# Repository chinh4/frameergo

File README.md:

# frameergo

An ergonomic laptop based off of the framework 13, based off of the concept by the Evan and Katelyn youtube channel. It will feature a keyboard based on the ferris sweep (though modified), and an adjustable display.

---

## Renders

images that look somewhat nice hopefully

---

## how use??!1/?

Put it together and enjoy... its pretty self explanatory. You can pivot the screen however you wish, as long as the cables reach.

CAD found [here](https://cad.onshape.com/documents/80817440b3423ec8b1940df3/w/df84cddcf0cb2965e0230ab6/e/d5c515e039b8b80401e512cd)

---

## but... why?

Why not? lol. More realistically, I wanted to do a project that challenged my current skillset and allow me to grow from it. Mainly with KiCAD and CAD in general.

---

## Frameortho (The keyboard)

---

## Display Adapters

---

## USB Hub

---

## BOM

| Item                          | Quantity             | Price (USD)   | Link                                                                                        | Description                       |
|:------------------------------|:---------------------|:--------------|:--------------------------------------------------------------------------------------------|:----------------------------------|
| PCB + Stencil (Sink + Source) | 5                    | $14.11        | https://jlcpcb.com/                                                                         | PCB for adapters                  |
| Display Port Cable            | 1                    | $7.50         | https://www.amazon.com/dp/B01J8S6X2I                                                        | Display Port cable                |
| 20455-040E-76                 | 2                    | $4.42         | https://www.digikey.com/en/products/detail/i-pex/20455-040E-76/22108829                     | EDP connector                     |
| XT30 (2+2) Right Male         | 2                    | $4.08         | https://www.aliexpress.us/item/3256804674449127.html                                        | Connector for power wires         |
| XT30 (2+2) Right Female       | 2                    | $4.44         | https://www.aliexpress.us/item/3256804674449127.html                                        | Connector for power               |
| Molex 0472720001              | 2                    | $11.06        | https://www.digikey.com/en/products/detail/molex/0472720001/1765727                         | Display Port connector            |
| EDP Cable                     | 1                    | $4.62         | https://www.aliexpress.us/item/3256806626687023.html                                        | EDP cable for display             |
| Flex PCB + Stencil            | 5                    | $5.05         | https://jlcpcb.com/                                                                         | USB Hub Flex Cable                |
| CY7C65634-28LTXC              | 5                    | $12.25        | https://www.digikey.com/en/products/detail/infineon-technologies/CY7C65634-28LTXC/2805204   | USB Hub IC                        |
| RR1220P-102-D                 | 10                   | $0.31         | https://www.digikey.com/en/products/detail/susumu/RR1220P-102-D/432291                      | 1k ohm resistor                   |
| CRCW080510K0FKEA              | 10                   | $0.41         | https://www.digikey.com/en/products/detail/vishay-dale/CRCW080510K0FKEA/1175751             | 10k ohm resistor                  |
| C0805C104K5RACTU              | 10                   | $0.16         | https://www.digikey.com/en/products/detail/kemet/C0805C104K5RACTU/411169                    | CAP CER 0.1UF 50V X7R 0805        |
| RMCF0805ZT0R00                | 10                   | $0.06         | https://www.digikey.com/en/products/detail/stackpole-electronics-inc/RMCF0805ZT0R00/1756901 | RES 0 OHM JUMPER 1/8W 0805        |
| ABM3B-12.000MHZ-B2-T          | 5                    | $3.35         | https://www.digikey.com/en/products/detail/abracon-llc/ABM3B-12-000MHZ-B2-T/675311          | CRYSTAL 12.0000MHZ 18PF SMD       |
| CC0805JRNPO9BN270             | 10                   | $0.48         | https://www.digikey.com/en/products/detail/yageo/CC0805JRNPO9BN270/302838                   | CAP CER 27PF 50V C0G/NPO 0805     |
| LMK212BJ106KG-T               | 10                   | $0.16         | https://www.digikey.com/en/products/detail/taiyo-yuden/LMK212BJ106KG-T/930652               | CAP CER 10UF 10V X5R 0805         |
| 046809610110846+              | 4                    | $2.84         | https://www.digikey.com/en/products/detail/kyocera-avx/046809610110846/10313169             | Power button connector            |
| PCB + PCBA                    | 2 (PCBA) + 3 (Blank) | $45.30        | https://jlcpcb.com/                                                                         | Keyboard PCB                      |
| PG1316S                       | 40                   | $30.00        | https://modulo.industries/product/pg1316s-switch/                                           | Keyswitches                       |
| SOD-123 Diode                 | 40                   | $30.00        | https://typeractive.xyz/products/smd-diodes                                                 | Diodes                            |
| TL3342                        | 2                    | $1.16         | https://www.digikey.com/en/products/base-product/e-switch/141/TL3342/472571                 | Buttons for boot and reset        |
| PG1316 Keycaps                | 4                    | $18.00        | https://holykeebs.com/products/kailh-pg1316s-keycaps?variant=49205120270626                 | Keycaps for keyswitches           |
| PETG Filament                 | 2                    | $24.99        | https://www.amazon.com/SUNLU-Filament-Strength-Dimensional-Accuracy/dp/B0FRRX8YDF           | Filament for case                 |
| Framework 13 Motherboard      | 1                    | Varies        | https://frame.work/marketplace/mainboards                                                   | Motherboard                       |
| Invisible Selfie Stick        | 4                    | $21.62        | https://www.aliexpress.us/item/3256805833609538.html                                        | For hinges and screen support     |
| Threaded bumper               | 2                    | $9.40         | https://www.mcmaster.com/9546K551/                                                          | For screen support                |
| 1/4 threaded inserts          | 1                    | $10.49        | https://www.amazon.com/dp/B08PVQX853                                                        | For screen frame                  |
| 1/4 Screw                     | 1                    | $8.49         | https://www.amazon.com/ThtRht-Replace-Handheld-Stabilizer-Extension/dp/B0FSRK4FYH           | For putting screen frame together |
| 1/4 x 1 - 1/2" Screw          | 1                    | $8.99         | https://www.amazon.com/Socket-Screws-Countersunk-Stainless-Thread/dp/B08QJ67SFG             | For putting hinges on             |
| 1/4 Nut                       | 1                    | $4.99         | https://www.amazon.com/Juvielich-4-20-Stainless-Fasteners-Replacement/dp/B0CSY9G7TW         | For putting hinges on             |
| Framework 13 Battery          | 1                    | $69.00        | https://frame.work/products/battery?v=FRANGWAT01                                            | Battery                           |
| Framework 13 Power Button     | 1                    | $29.00        | https://frame.work/products/fingerprint-reader-kit?v=FRANTD0001                             | Power button                      |
| Framework 13 Touchpad         | 1                    | $39.00        | https://frame.work/products/touchpad-kit?v=FRANFT0001                                       | Touchpad                          |
| Framework 13 Screen           | 1                    | $159.00       | https://frame.work/products/display-kit?v=FRANGX0001                                        | Screen                            |
| Framework 13 Audio Board      | 1                    | $14.00        | https://frame.work/products/audio-board-kit?v=FRANFY0001                                    | Audio board                       |
| Framework 13 Antenna          | 1                    | $14.00        | https://frame.work/products/antenna-module?v=FRANCXAW01                                     |                                   |
| Total (no tax or shipping):   |                      | $612.73       |                                                                                             |                                   |

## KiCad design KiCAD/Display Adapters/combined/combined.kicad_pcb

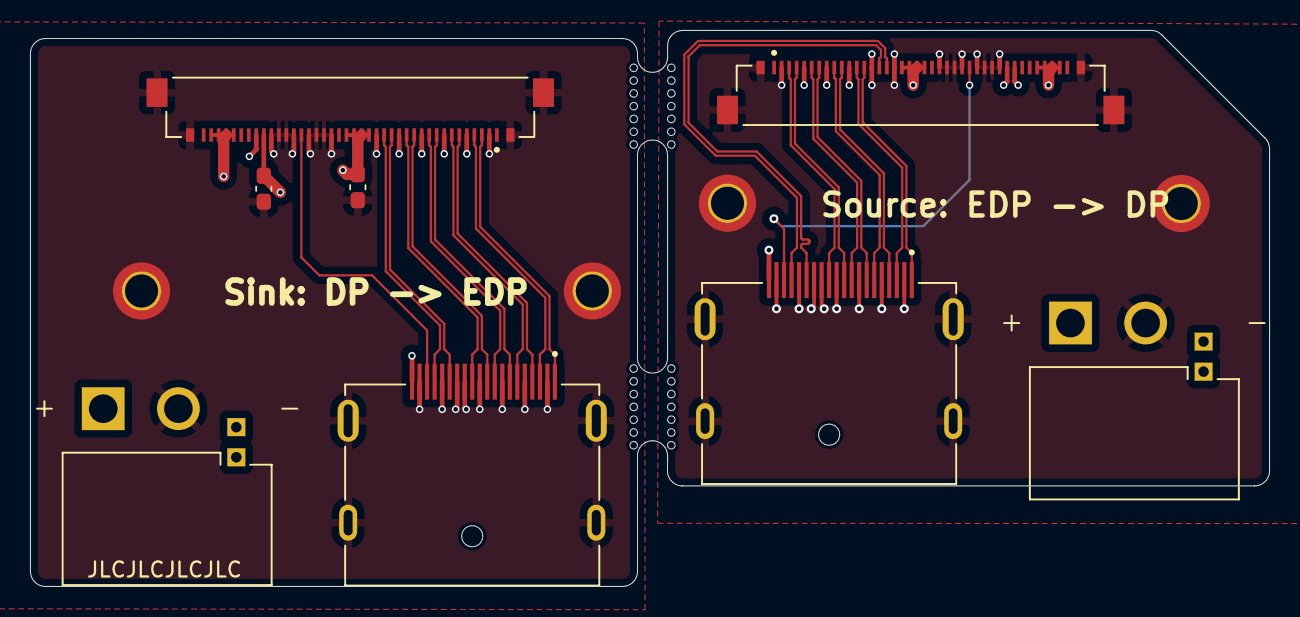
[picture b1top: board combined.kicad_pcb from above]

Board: 4 copper layers, 82.4 x 37.0 mm, 12 parts (0 on the bottom side), 16 nets.

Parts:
C1, C2: 1uF; C_0603_1608Metric_Pad1.08x0.95mm_HandSolder
H1, H1#2, H2, H2#2: MountingHole_Pad; MountingHole_2.2mm_M2_DIN965_Pad_TopBottom
J1, J4: 47272-0001; MOLEX_47272-0001
J2, J5: XT30PW_2_2_-M.G.B; AMASS_XT30PW_2_2_-M.G.B
J3, J6: 20455-040E-76; IPEX_20455-040E-76

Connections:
0_EDP_TX_N: J1.10, J3.12, J4.3, J6.12
0_EDP_TX_P: J1.12, J3.13, J4.1, J6.13
1_EDP_TX_N: J1.7, J3.9, J4.6, J6.9
1_EDP_TX_P: J1.9, J3.10, J4.4, J6.10
2_EDP_TX_N: J1.4, J3.6, J4.9, J6.6
2_EDP_TX_P: J1.6, J3.7, J4.7, J6.7
3_EDP_TX_N: J1.1, J3.3, J4.12, J6.3
3_EDP_TX_P: J1.3, J3.4, J4.10, J6.4
+3.3V: C1.1, J1.20, J3.18, J3.19, J3.20, J3.21, J4.20, J6.18, J6.19, J6.20, J6.21
+5V: J2.P, J3.36, J3.37, J3.38, J3.39, J5.P, J6.36, J6.37, J6.38, J6.39
AUX_N: J1.17, J3.16, J4.17, J6.16
AUX_P: J1.15, J3.15, J4.15, J6.15
BLK_OFF_N: C2.2, J2.S1, J3.32, J5.S1, J6.32
BLK_PWM_LCD: J2.S2, J3.33, J5.S2, J6.33
EDP_HPD: J1.18, J3.27, J4.18, J6.27
GND: C1.2, C2.1, H1.1, H1#2.1, H2.1, H2#2.1, J1.2, J1.5, J1.8, J1.11, J1.13, J1.14, J1.16, J1.19, J1.S1 (SHIELD), J1.S2 (SHIELD), J1.S3 (SHIELD), J1.S4 (SHIELD), J2.N, J3.2, J3.5, J3.8, J3.11, J3.14, J3.17, J3.23, J3.24, J3.25, J3.26, J3.28, J3.29, J3.30, J3.31, J3.S1 (SHIELD), J3.S2 (SHIELD), J3.S3 (SHIELD), J3.S4 (SHIELD), J4.2, J4.5, J4.8, J4.11, J4.13, J4.14, J4.16, J4.19, J4.S1 (SHIELD), J4.S2 (SHIELD), J4.S3 (SHIELD), J4.S4 (SHIELD), J5.N, J6.2, J6.5, J6.8, J6.11, J6.14, J6.17, J6.23, J6.24, J6.25, J6.26, J6.28, J6.29, J6.30, J6.31, J6.S1 (SHIELD), J6.S2 (SHIELD), J6.S3 (SHIELD), J6.S4 (SHIELD)

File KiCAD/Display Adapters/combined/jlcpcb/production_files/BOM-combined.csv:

Comment,Designator,Footprint,LCSC,Quantity
1uF,"C1,C2",C_0603_1608Metric_Pad1.08x0.95mm_HandSolder,C14663,2
20455-040E-76,"J3,J6",IPEX_20455-040E-76,C5160883,2
47272-0001,"J1,J4",MOLEX_47272-0001,C587824,2

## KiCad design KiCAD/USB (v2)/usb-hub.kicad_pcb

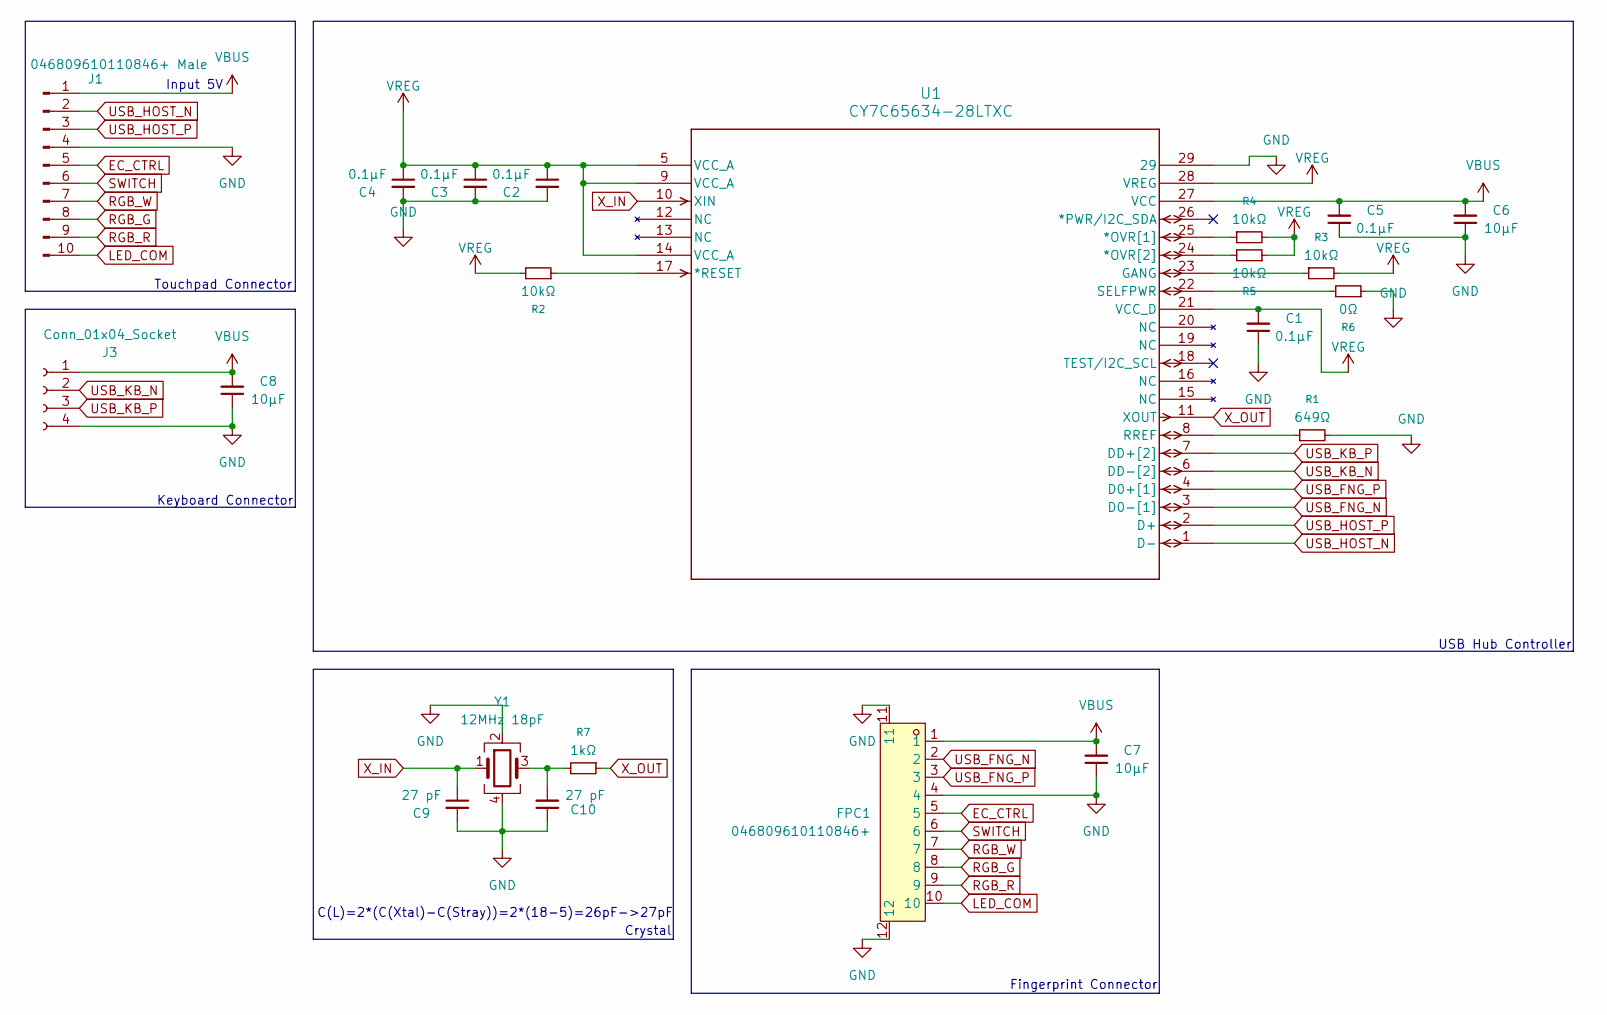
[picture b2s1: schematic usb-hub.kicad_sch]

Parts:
C1, C2, C3, C4, C5: 0.1μF; C_0805_2012Metric_Pad1.18x1.45mm_HandSolder
C6, C7, C8: 10μF; C_0805_2012Metric_Pad1.18x1.45mm_HandSolder
C9, C10: 27 pF; C_0805_2012Metric_Pad1.18x1.45mm_HandSolder
FPC1: 046809610110846+; CONN-SMD_10P-P0.50_046809610110846; LCSC Part C5464531
J1: 046809610110846+ Male; Kyocera_046809610110846+_PCB_Edge
J3: Conn_01x04_Socket; 4 pad
R1: 649Ω; R_0805_2012Metric_Pad1.20x1.40mm_HandSolder
R2, R3, R4, R5: 10kΩ; R_0805_2012Metric_Pad1.20x1.40mm_HandSolder
R6: 0Ω; R_0805_2012Metric_Pad1.20x1.40mm_HandSolder
R7: 1kΩ; R_0805_2012Metric_Pad1.20x1.40mm_HandSolder
U1: CY7C65634-28LTXC; QFN-28
Y1: 12MHz 18pF; Crystal_SMD_Abracon_ABM3B-4Pin_5.0x3.2mm

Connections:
EC_CTRL: FPC1.5, J1.5
GND: C1.1, C2.2, C3.2, C4.2, C5.1, C6.1, C7.1, C8.1, C9.2, C10.1, FPC1.4, FPC1.11, FPC1.12, J1.4, J3.4, R1.2, R6.1, U1.29, Y1.2, Y1.4
LED_COM: FPC1.10, J1.10
unnamed: C10.2, R7.2, Y1.3
unnamed: R4.1, U1.25 (*OVR[1])
unnamed: R5.2, U1.24 (*OVR[2])
unnamed: R2.1, U1.17 (*RESET)
unnamed: R3.1, U1.23 (GANG)
unnamed: R1.1, U1.8 (RREF)
unnamed: R6.2, U1.22 (SELFPWR)
RGB_G: FPC1.8, J1.8
RGB_R: FPC1.9, J1.9
RGB_W: FPC1.7, J1.7
SWITCH: FPC1.6, J1.6
USB_FNG_N: FPC1.2, U1.3 (D0-[1])
USB_FNG_P: FPC1.3, U1.4 (D0+[1])
USB_HOST_N: J1.2, U1.1 (D-)
USB_HOST_P: J1.3, U1.2 (D+)
USB_KB_N: J3.2, U1.6 (DD-[2])
USB_KB_P: J3.3, U1.7 (DD+[2])
VBUS: C5.2, C6.2, C7.2, C8.2, FPC1.1, J1.1, J3.1, U1.27 (VCC)
VREG: C1.2, C2.1, C3.1, C4.1, R2.2, R3.2, R4.2, R5.1, U1.5 (VCC_A), U1.9 (VCC_A), U1.14 (VCC_A), U1.21 (VCC_D), U1.28 (VREG)
X_IN: C9.1, U1.10 (XIN), Y1.1
X_OUT: R7.1, U1.11 (XOUT)

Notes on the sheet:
USB Hub Controller
Keyboard Connector
Crystal
Touchpad Connector
Fingerprint Connector
C(L)=2*(C(Xtal)-C(Stray))=2*(18-5)=26pF->27pF
Input 5V

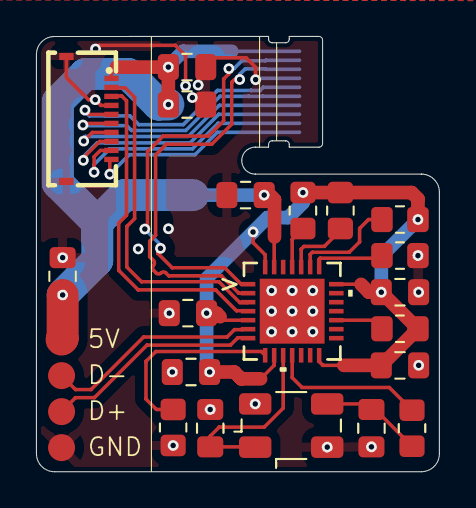
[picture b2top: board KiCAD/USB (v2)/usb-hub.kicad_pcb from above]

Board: 2 copper layers, 22.4 x 24.2 mm, 22 parts (0 on the bottom side), 24 nets.

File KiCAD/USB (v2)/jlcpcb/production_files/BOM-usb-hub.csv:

Comment,Designator,Footprint,LCSC,Quantity
046809610110846+,FPC1,CONN-SMD_10P-P0.50_046809610110846,C5464531,1
CY7C65634-28LTXC,U1,QFN-28,C2951393,1
10kΩ,R5,R_0805_2012Metric_Pad1.20x1.40mm_HandSolder,,1
10kΩ,R4,R_0805_2012Metric_Pad1.20x1.40mm_HandSolder,,1
10kΩ,R2,R_0805_2012Metric_Pad1.20x1.40mm_HandSolder,,1
0.1μF,C4,C_0805_2012Metric_Pad1.18x1.45mm_HandSolder,,1
0.1μF,C5,C_0805_2012Metric_Pad1.18x1.45mm_HandSolder,,1
649Ω,R1,R_0805_2012Metric_Pad1.20x1.40mm_HandSolder,,1
0.1μF,C1,C_0805_2012Metric_Pad1.18x1.45mm_HandSolder,,1
10μF,C8,C_0805_2012Metric_Pad1.18x1.45mm_HandSolder,,1
10kΩ,R3,R_0805_2012Metric_Pad1.20x1.40mm_HandSolder,,1
27 pF,C10,C_0805_2012Metric_Pad1.18x1.45mm_HandSolder,,1
0Ω,R6,R_0805_2012Metric_Pad1.20x1.40mm_HandSolder,,1
12MHz 18pF,Y1,Crystal_SMD_Abracon_ABM3B-4Pin_5.0x3.2mm,,1
0.1μF,C2,C_0805_2012Metric_Pad1.18x1.45mm_HandSolder,,1
27 pF,C9,C_0805_2012Metric_Pad1.18x1.45mm_HandSolder,,1
10μF,C6,C_0805_2012Metric_Pad1.18x1.45mm_HandSolder,,1
1kΩ,R7,R_0805_2012Metric_Pad1.20x1.40mm_HandSolder,,1
0.1μF,C3,C_0805_2012Metric_Pad1.18x1.45mm_HandSolder,,1
10μF,C7,C_0805_2012Metric_Pad1.18x1.45mm_HandSolder,,1

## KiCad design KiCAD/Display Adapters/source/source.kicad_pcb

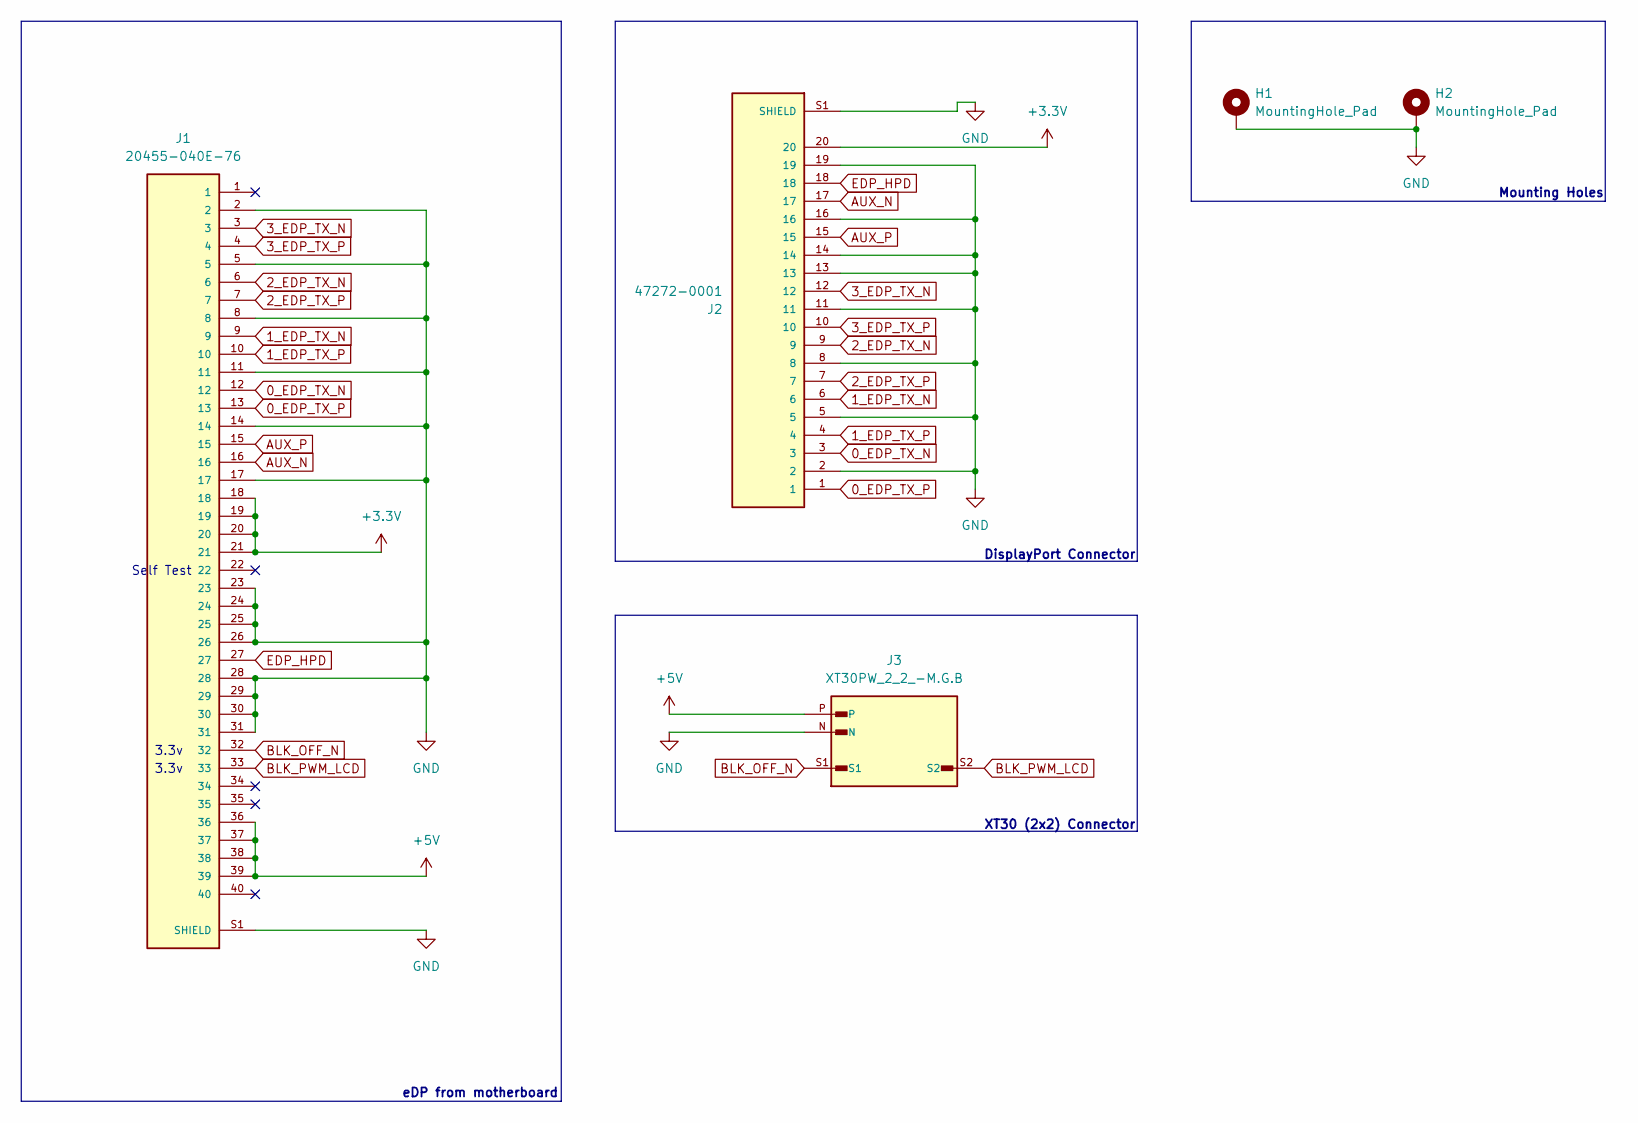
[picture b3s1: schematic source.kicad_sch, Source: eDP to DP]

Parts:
H1, H2: MountingHole_Pad; MountingHole_2.2mm_M2_DIN965_Pad_TopBottom
J1: 20455-040E-76; IPEX_20455-040E-76
J2: 47272-0001; MOLEX_47272-0001
J3: XT30PW_2_2_-M.G.B; AMASS_XT30PW_2_2_-M.G.B; PARTREV NA

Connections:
0_EDP_TX_N: J1.12, J2.3
0_EDP_TX_P: J1.13, J2.1
1_EDP_TX_N: J1.9, J2.6
1_EDP_TX_P: J1.10, J2.4
2_EDP_TX_N: J1.6, J2.9
2_EDP_TX_P: J1.7, J2.7
3_EDP_TX_N: J1.3, J2.12
3_EDP_TX_P: J1.4, J2.10
+3.3V: J1.18, J1.19, J1.20, J1.21, J2.20
+5V: J1.36, J1.37, J1.38, J1.39, J3.P
AUX_N: J1.16, J2.17
AUX_P: J1.15, J2.15
BLK_OFF_N: J1.32, J3.S1
BLK_PWM_LCD: J1.33, J3.S2
EDP_HPD: J1.27, J2.18
GND: H1.1, H2.1, J1.2, J1.5, J1.8, J1.11, J1.14, J1.17, J1.23, J1.24, J1.25, J1.26, J1.28, J1.29, J1.30, J1.31, J1.S1 (SHIELD), J1.S2 (SHIELD), J1.S3 (SHIELD), J1.S4 (SHIELD), J2.2, J2.5, J2.8, J2.11, J2.13, J2.14, J2.16, J2.19, J2.S1 (SHIELD), J2.S2 (SHIELD), J2.S3 (SHIELD), J2.S4 (SHIELD), J3.N

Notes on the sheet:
3.3v
eDP from motherboard
DisplayPort Connector
Mounting Holes
XT30 (2x2) Connector
Self Test

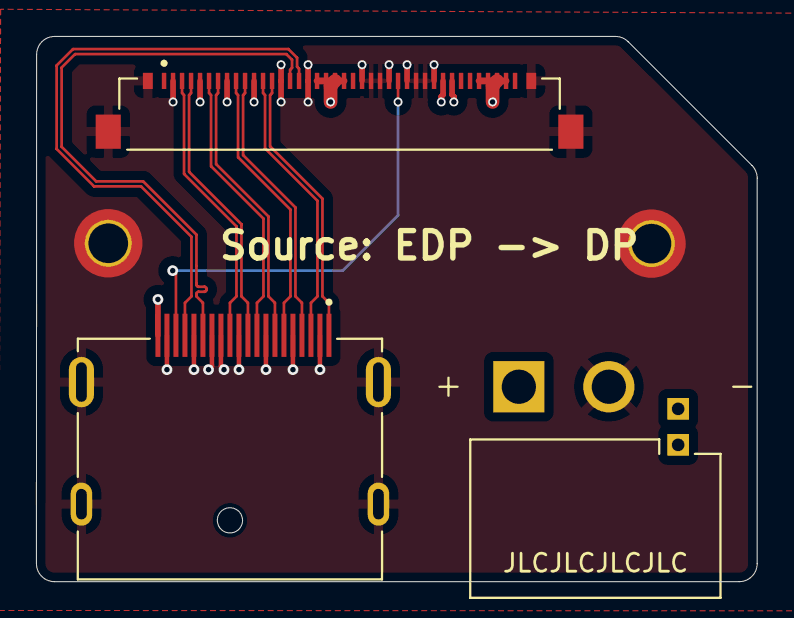
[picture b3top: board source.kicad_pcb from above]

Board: 4 copper layers, 40.0 x 30.3 mm, 5 parts (0 on the bottom side), 16 nets.

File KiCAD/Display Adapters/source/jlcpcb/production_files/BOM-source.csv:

Comment,Designator,Footprint,LCSC,Quantity
20455-040E-76,J1,IPEX_20455-040E-76,C5160883,1
47272-0001,J2,MOLEX_47272-0001,C587824,1

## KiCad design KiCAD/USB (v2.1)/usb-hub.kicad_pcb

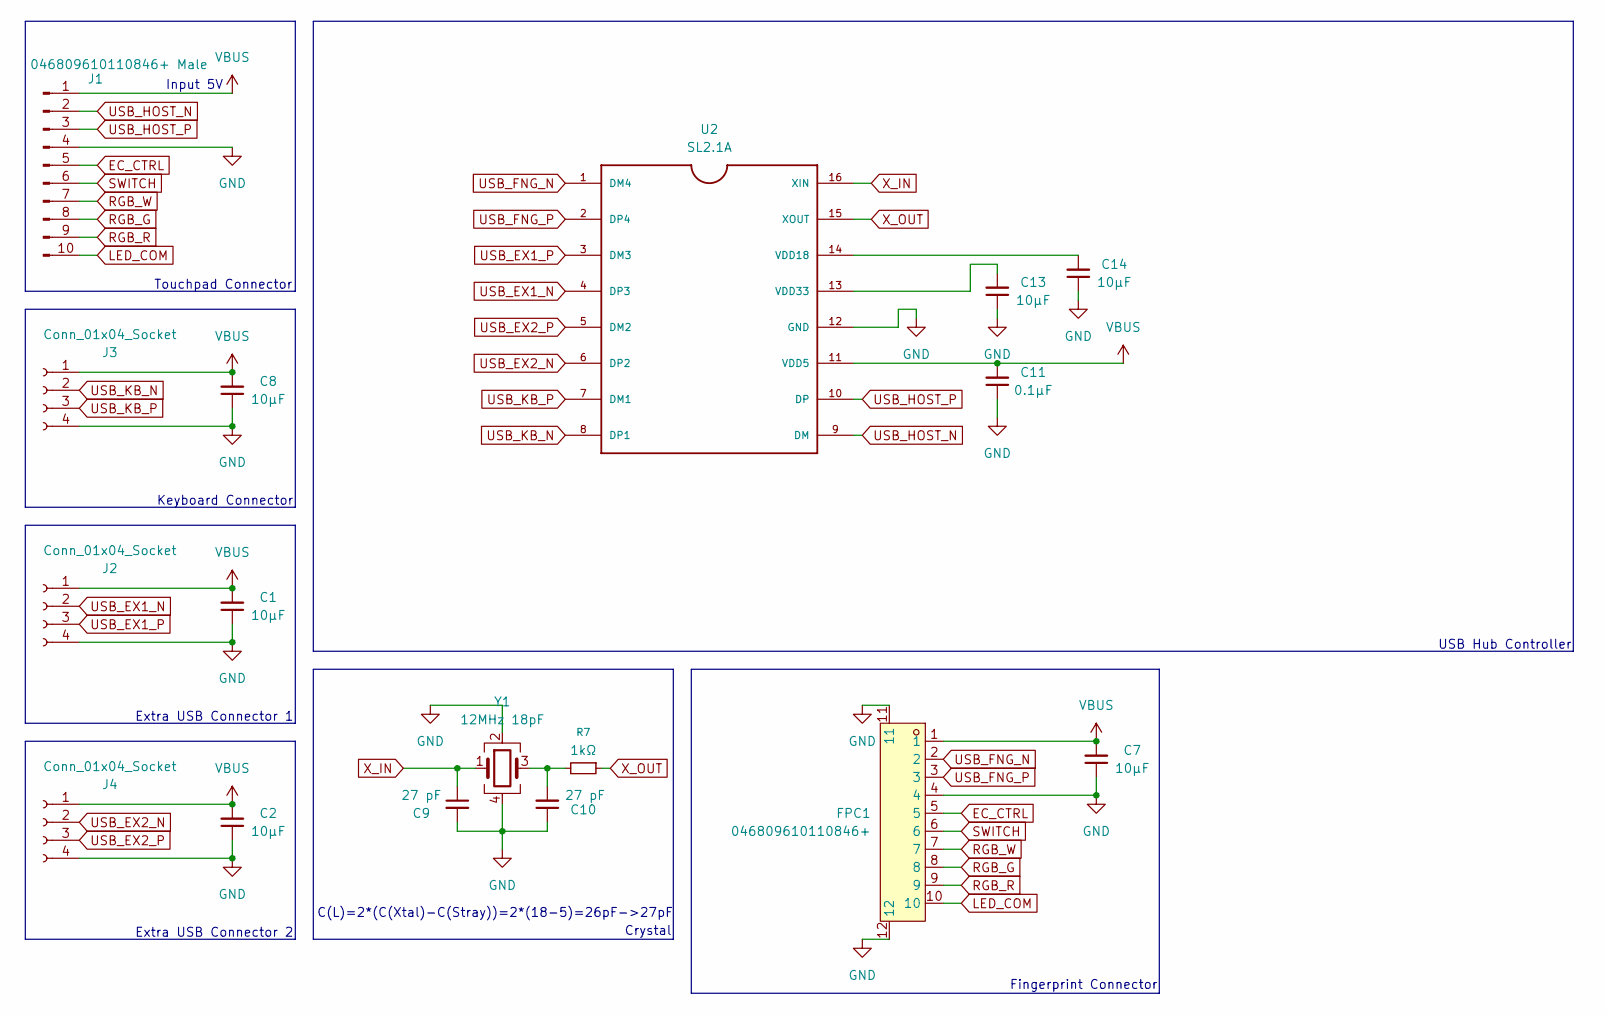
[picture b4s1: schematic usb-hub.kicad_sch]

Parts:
C1, C2, C7, C8, C13, C14: 10μF; C_0805_2012Metric_Pad1.18x1.45mm_HandSolder
C9, C10: 27 pF; C_0805_2012Metric_Pad1.18x1.45mm_HandSolder
C11: 0.1μF; C_0805_2012Metric_Pad1.18x1.45mm_HandSolder
FPC1: 046809610110846+; CONN-SMD_10P-P0.50_046809610110846; LCSC Part C5464531
J1: 046809610110846+ Male; Kyocera_046809610110846+_PCB_Edge
J2, J3, J4: Conn_01x04_Socket; 4 pad
R7: 1kΩ; R_0805_2012Metric_Pad1.20x1.40mm_HandSolder
U2: SL2.1A; SO16
Y1: 12MHz 18pF; Crystal_SMD_Abracon_ABM3B-4Pin_5.0x3.2mm

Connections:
EC_CTRL: FPC1.5, J1.5
GND: C1.1, C2.1, C7.1, C8.1, C9.2, C10.1, C11.1, C13.1, C14.1, FPC1.4, FPC1.11, FPC1.12, J1.4, J2.4, J3.4, J4.4, U2.12 (GND), Y1.2, Y1.4; also elsewhere on the board
LED_COM: FPC1.10, J1.10
unnamed: C10.2, R7.2, Y1.3
unnamed: C14.2, U2.14 (VDD18)
unnamed: C13.2, U2.13 (VDD33)
RGB_G: FPC1.8, J1.8
RGB_R: FPC1.9, J1.9
RGB_W: FPC1.7, J1.7
SWITCH: FPC1.6, J1.6
USB_EX1_N: J2.2, U2.4 (DP3)
USB_EX1_P: J2.3, U2.3 (DM3)
USB_EX2_N: J4.2, U2.6 (DP2)
USB_EX2_P: J4.3, U2.5 (DM2)
USB_FNG_N: FPC1.2, U2.1 (DM4)
USB_FNG_P: FPC1.3, U2.2 (DP4)
USB_HOST_N: J1.2, U2.9 (DM)
USB_HOST_P: J1.3, U2.10 (DP)
USB_KB_N: J3.2, U2.8 (DP1)
USB_KB_P: J3.3, U2.7 (DM1)
VBUS: C1.2, C2.2, C7.2, C8.2, C11.2, FPC1.1, J1.1, J2.1, J3.1, J4.1, U2.11 (VDD5); also elsewhere on the board
X_IN: C9.1, U2.16 (XIN), Y1.1
X_OUT: R7.1, U2.15 (XOUT)

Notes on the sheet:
USB Hub Controller
Extra USB Connector 1
Keyboard Connector
Extra USB Connector 2
Crystal
Touchpad Connector
Fingerprint Connector
C(L)=2*(C(Xtal)-C(Stray))=2*(18-5)=26pF->27pF
Input 5V

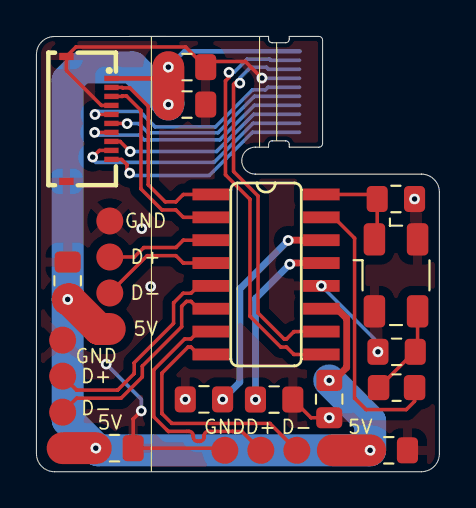
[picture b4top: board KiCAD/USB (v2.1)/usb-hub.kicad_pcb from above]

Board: 2 copper layers, 22.4 x 24.2 mm, 18 parts (0 on the bottom side), 23 nets.

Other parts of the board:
C6: 10μF; C_0805_2012Metric_Pad1.18x1.45mm_HandSolder

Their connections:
GND: C6.1; also elsewhere on the board
VBUS: C6.2; also elsewhere on the board

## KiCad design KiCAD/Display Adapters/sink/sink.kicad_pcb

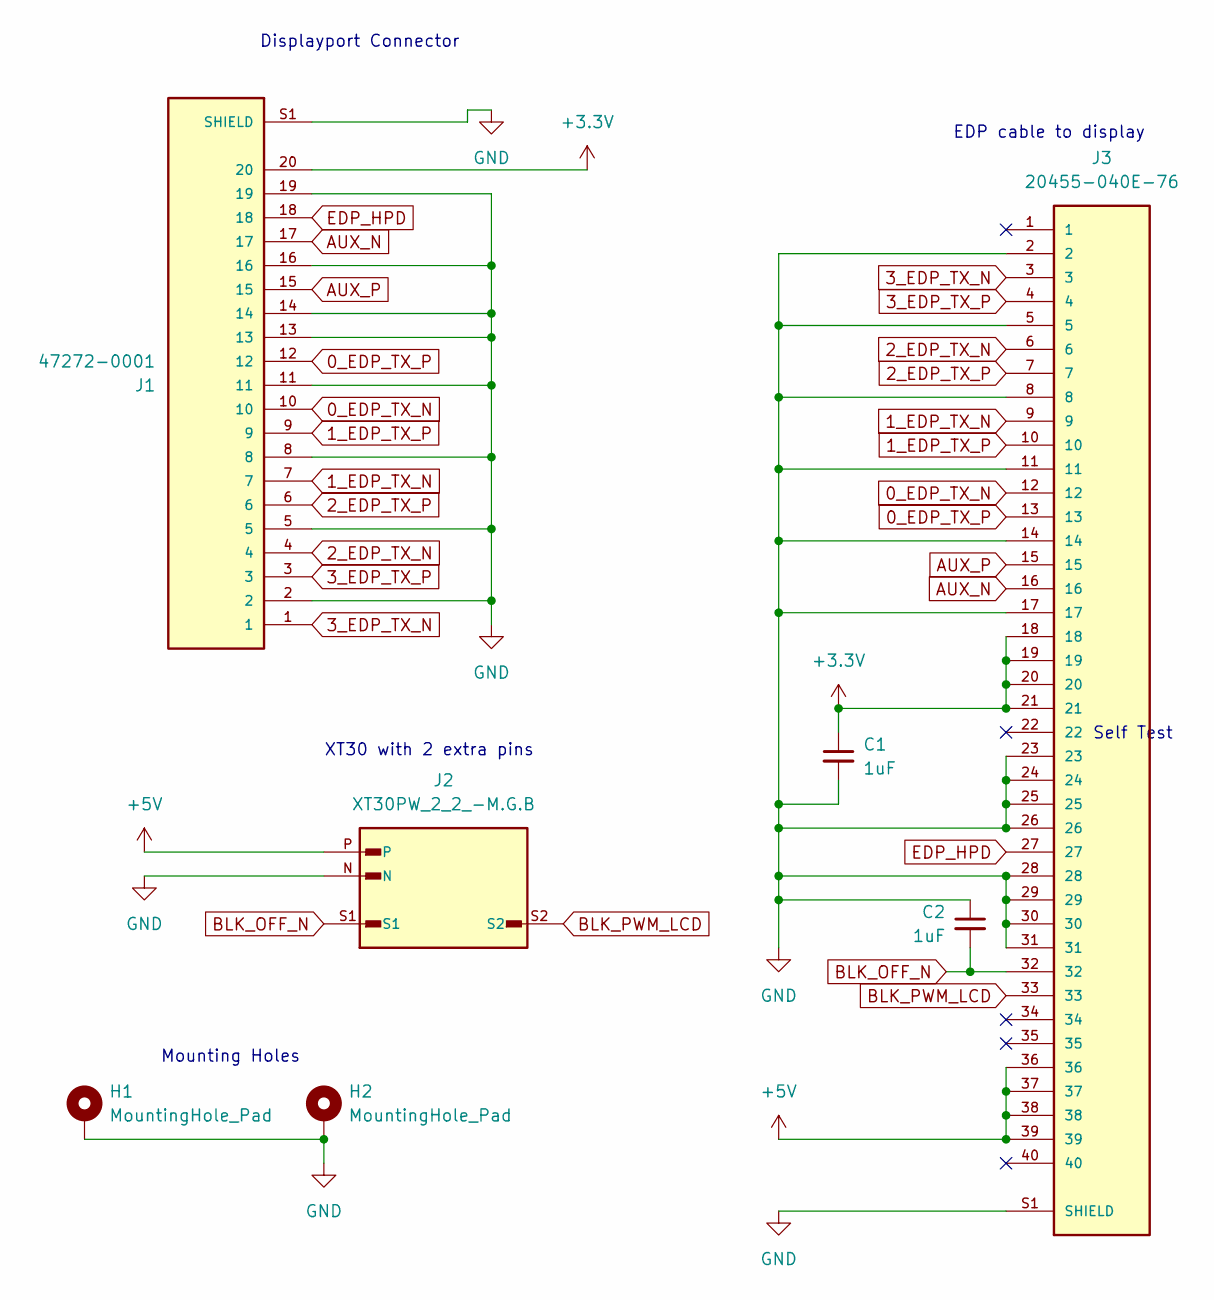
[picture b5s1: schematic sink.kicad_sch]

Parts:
C1, C2: 1uF; C_0603_1608Metric_Pad1.08x0.95mm_HandSolder
H1, H2: MountingHole_Pad; MountingHole_2.2mm_M2_DIN965_Pad_TopBottom
J1: 47272-0001; MOLEX_47272-0001
J2: XT30PW_2_2_-M.G.B; AMASS_XT30PW_2_2_-M.G.B; PARTREV NA
J3: 20455-040E-76; IPEX_20455-040E-76

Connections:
0_EDP_TX_N: J1.10, J3.12
0_EDP_TX_P: J1.12, J3.13
1_EDP_TX_N: J1.7, J3.9
1_EDP_TX_P: J1.9, J3.10
2_EDP_TX_N: J1.4, J3.6
2_EDP_TX_P: J1.6, J3.7
3_EDP_TX_N: J1.1, J3.3
3_EDP_TX_P: J1.3, J3.4
+3.3V: C1.1, J1.20, J3.18, J3.19, J3.20, J3.21
+5V: J2.P, J3.36, J3.37, J3.38, J3.39
AUX_N: J1.17, J3.16
AUX_P: J1.15, J3.15
BLK_OFF_N: C2.2, J2.S1, J3.32
BLK_PWM_LCD: J2.S2, J3.33
EDP_HPD: J1.18, J3.27
GND: C1.2, C2.1, H1.1, H2.1, J1.2, J1.5, J1.8, J1.11, J1.13, J1.14, J1.16, J1.19, J1.S1 (SHIELD), J1.S2 (SHIELD), J1.S3 (SHIELD), J1.S4 (SHIELD), J2.N, J3.2, J3.5, J3.8, J3.11, J3.14, J3.17, J3.23, J3.24, J3.25, J3.26, J3.28, J3.29, J3.30, J3.31, J3.S1 (SHIELD), J3.S2 (SHIELD), J3.S3 (SHIELD), J3.S4 (SHIELD)

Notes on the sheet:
EDP cable to display
Displayport Connector
Mounting Holes
Self Test
XT30 with 2 extra pins

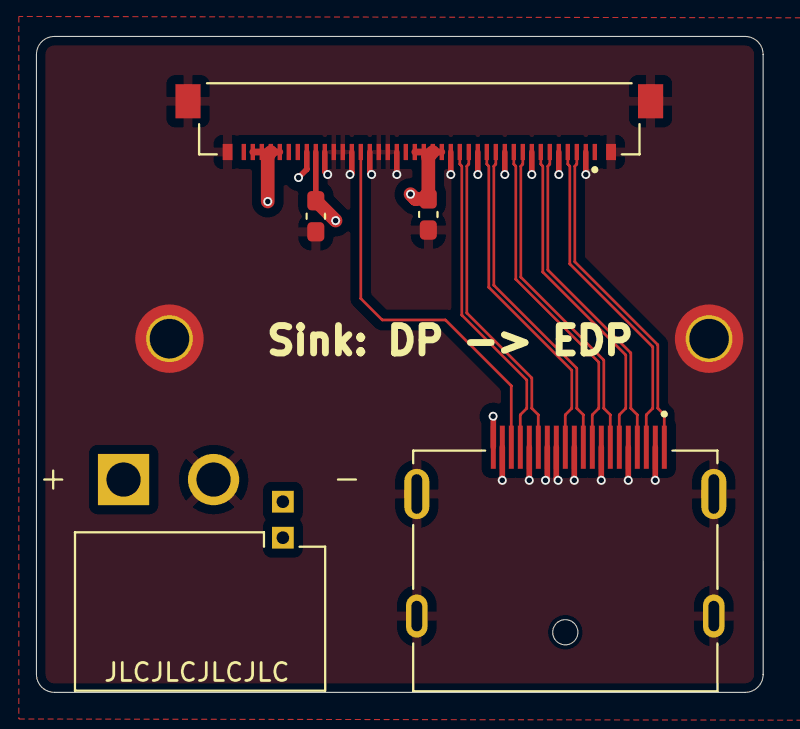
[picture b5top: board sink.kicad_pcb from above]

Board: 4 copper layers, 40.4 x 36.4 mm, 7 parts (0 on the bottom side), 16 nets.

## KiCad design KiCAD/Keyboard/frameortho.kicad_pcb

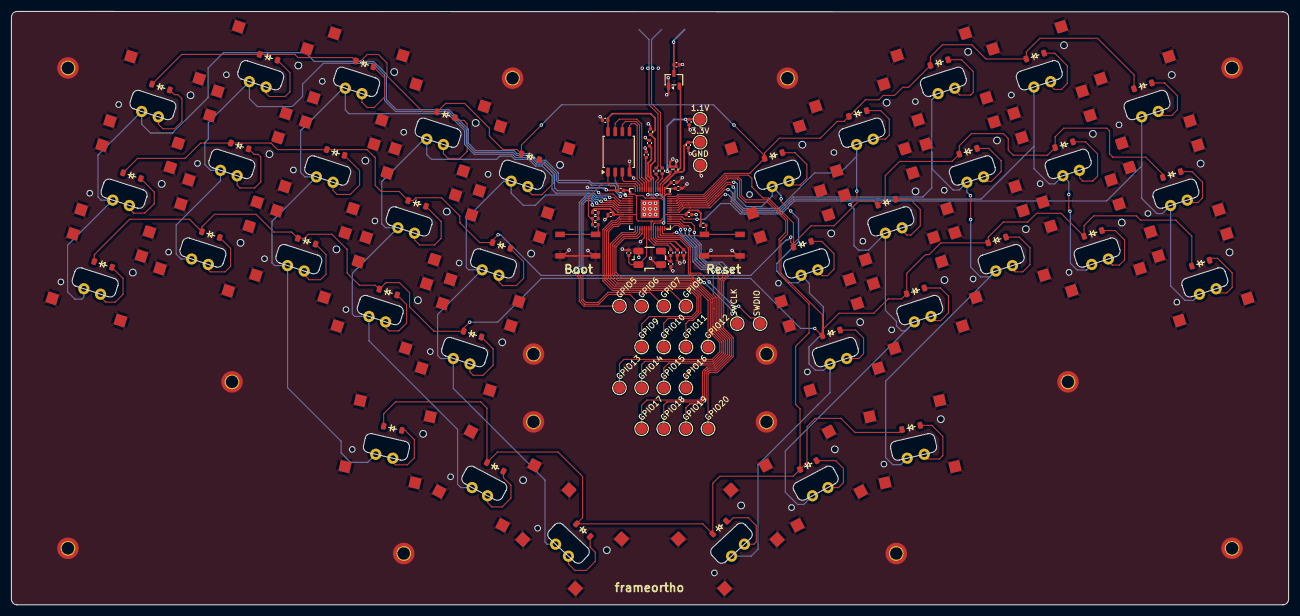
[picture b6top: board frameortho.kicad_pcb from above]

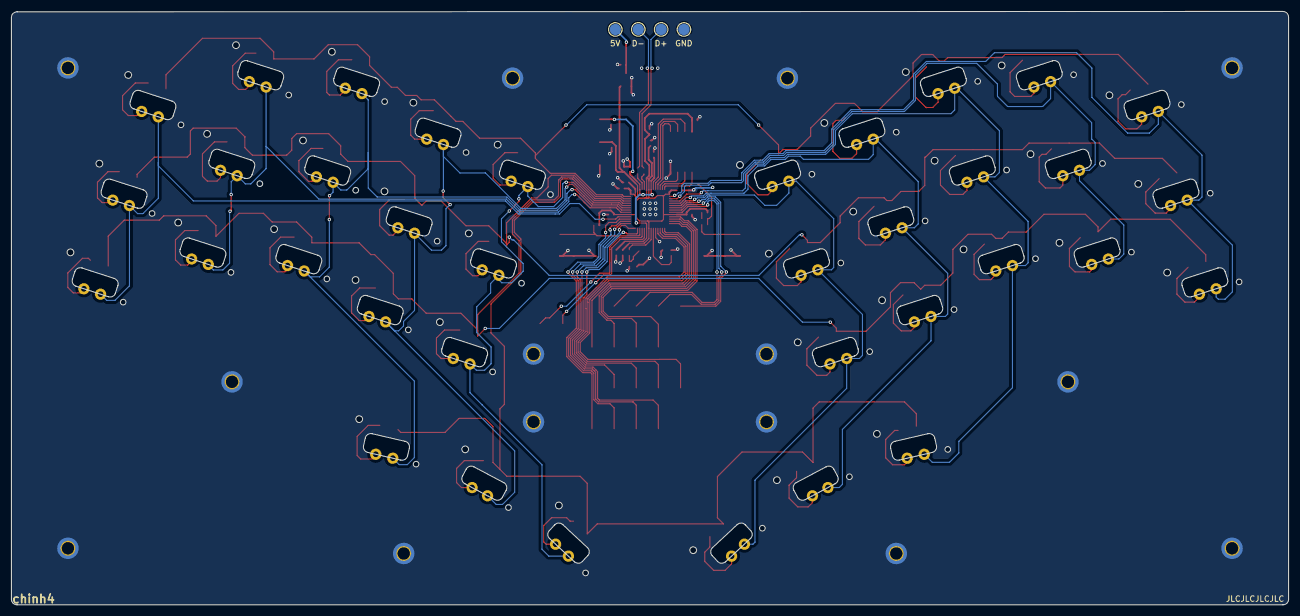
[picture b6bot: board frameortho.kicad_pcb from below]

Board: 2 copper layers, 225.9 x 104.9 mm, 142 parts (4 on the bottom side), 88 nets.

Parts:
1.1V, 3.3V: TestPoint; TestPoint_Pad_D2.0mm
C1, C2, C11, C16: 1µF; C_0402_1005Metric
C3, C4, C5, C6, C7, C8, C9, C10, C12, C13, C17, C18: 100nF; C_0402_1005Metric
C14, C15: 27pF; C_0402_1005Metric
D1, D2, D3, D4, D5, D6, D7, D8, D9, D10, D11, D12, D13, D14, D15, D16, D17, D18, D19, D20, D21, D22, D23, D24, D25, D26, D27, D28, D29, D30, D31, D32, D33, D34, D35, D36: D_Small; Diode_SOD-123
GND: TestPoint; TestPoint_Pad_D2.0mm
H1, H2, H3, H4, H5, H5#2, H6, H7, H8, H9, H10, H11, H12, H13: MountingHole_Pad; MountingHole_2.2mm_M2_DIN965_Pad_TopBottom
R3, R4: 27Ω; R_0402_1005Metric
R5, R7, R8: 5.1kΩ; R_0402_1005Metric
R6, R9: 1kΩ; R_0402_1005Metric
S1, S2, S3, S4, S5, S6, S7, S8, S9, S10, S11, S12, S13, S14, S15, S16, S17, S18, S19, S20, S21, S22, S23, S24, S25, S26, S27, S28, S29, S30, S31, S32, S33, S34, S35, S36: Keyswitch; CPG1316S01D02_castelated_mikecinq
SW1, SW2: SW_Push; Button_TL3342
TP1, TP2, TP3, TP4, TP5, TP6, TP7, TP8, TP9, TP10, TP11, TP12, TP13, TP14, TP15, TP16, TP17, TP18, TP19, TP20, TP21, TP22: TestPoint; TestPoint_Pad_D2.0mm
U1: RP2040; QFN-56-1EP_7x7mm_P0.4mm_EP3.2x3.2mm
U2: W25Q128JVS; SOIC-8_5.3x5.3mm_P1.27mm
U3: XC6206PxxxMR; SOT-23-3
Y1: 12 MHz 18pF; Crystal_SMD_Abracon_ABM3B-4Pin_5.0x3.2mm

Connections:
+1V1: 1.1V.1, C11.1, C12.1, C13.1, C18.1, U1.23 (DVDD), U1.45 (VREG_VOUT), U1.50 (DVDD)
+3V3: 3.3V.1, C1.1, C2.1, C3.1, C4.1, C5.1, C6.1, C7.1, C8.1, C9.1, C10.1, C17.1, R5.1, R7.1, U1.1 (IOVDD), U1.10 (IOVDD), U1.22 (IOVDD), U1.33 (IOVDD), U1.42 (IOVDD), U1.43 (ADC_AVDD), U1.44 (VREG_IN), U1.48 (USB_VDD), U1.49 (IOVDD), U2.8 (VCC), U3.2 (VO)
+5V: C16.1, TP17.1, U3.3 (VI)
COL_0: S1.1, S11.1, S21.1, U1.2 (GPIO0)
COL_1: S2.1, S12.1, S22.1, U1.3 (GPIO1)
COL_2: S3.1, S13.1, S23.1, S31.1, U1.4 (GPIO2)
COL_3: S4.1, S14.1, S24.1, S32.1, U1.5 (GPIO3)
COL_4: S5.1, S15.1, S25.1, S33.1, U1.6 (GPIO4)
COL_5: S6.1, S16.1, S26.1, S34.1, U1.37 (GPIO25)
COL_6: S7.1, S17.1, S27.1, S35.1, U1.36 (GPIO24)
COL_7: S8.1, S18.1, S28.1, S36.1, U1.35 (GPIO23)
COL_8: S9.1, S19.1, S29.1, U1.34 (GPIO22)
COL_9: S10.1, S20.1, S30.1, U1.32 (GPIO21)
D_N: R4.2, TP19.1
D_P: R3.2, TP18.1
GND: C1.2, C2.2, C3.2, C4.2, C5.2, C6.2, C7.2, C8.2, C9.2, C10.2, C11.2, C12.2, C13.2, C14.1, C15.1, C16.2, C17.2, C18.2, GND.1, H1.1, H2.1, H3.1, H4.1, H5.1, H5#2.1, H6.1, H7.1, H8.1, H9.1, H10.1, H11.1, H12.1, H13.1, S1.3, S2.3, S3.3, S4.3, S5.3, S6.3, S7.3, S8.3, S9.3, S10.3, S11.3, S12.3, S13.3, S14.3, S15.3, S16.3, S17.3, S18.3, S19.3, S20.3, S21.3, S22.3, S23.3, S24.3, S25.3, S26.3, S27.3, S28.3, S29.3, S30.3, S31.3, S32.3, S33.3, S34.3, S35.3, S36.3, SW1.1, SW2.1, TP20.1, U1.19 (TESTEN), U1.57 (GND), U2.4 (GND), U3.1 (GND), Y1.2, Y1.4
GPIO5: TP1.1, U1.7 (GPIO5)
GPIO6: TP2.1, U1.8 (GPIO6)
GPIO7: TP3.1, U1.9 (GPIO7)
GPIO8: TP4.1, U1.11 (GPIO8)
GPIO9: TP5.1, U1.12 (GPIO9)
GPIO10: TP6.1, U1.13 (GPIO10)
GPIO11: TP7.1, U1.14 (GPIO11)
GPIO12: TP8.1, U1.15 (GPIO12)
GPIO13: TP9.1, U1.16 (GPIO13)
GPIO14: TP10.1, U1.17 (GPIO14)
GPIO15: TP11.1, U1.18 (GPIO15)
GPIO16: TP12.1, U1.27 (GPIO16)
GPIO17: TP13.1, U1.28 (GPIO17)
GPIO18: TP14.1, U1.29 (GPIO18)
GPIO19: TP15.1, U1.30 (GPIO19)
GPIO20: TP16.1, U1.31 (GPIO20)
unnamed: C15.2, R6.1, Y1.3
unnamed: D1.2 (A), S1.2
unnamed: D2.2 (A), S2.2
unnamed: D3.2 (A), S3.2
unnamed: D4.2 (A), S4.2
unnamed: D5.2 (A), S5.2
unnamed: D6.2 (A), S6.2
unnamed: D7.2 (A), S7.2
unnamed: D8.2 (A), S8.2
unnamed: D9.2 (A), S9.2
unnamed: D10.2 (A), S10.2
unnamed: D11.2 (A), S11.2
unnamed: D12.2 (A), S12.2
unnamed: D13.2 (A), S13.2
unnamed: D14.2 (A), S14.2
unnamed: D15.2 (A), S15.2
unnamed: D16.2 (A), S16.2
unnamed: D17.2 (A), S17.2
unnamed: D18.2 (A), S18.2
unnamed: D19.2 (A), S19.2
unnamed: D20.2 (A), S20.2
unnamed: D21.2 (A), S21.2
unnamed: D22.2 (A), S22.2
unnamed: D23.2 (A), S23.2
unnamed: D24.2 (A), S24.2
unnamed: D25.2 (A), S25.2
unnamed: D26.2 (A), S26.2
unnamed: D27.2 (A), S27.2
unnamed: D28.2 (A), S28.2
unnamed: D29.2 (A), S29.2
unnamed: D30.2 (A), S30.2
unnamed: D31.2 (A), S31.2
unnamed: D32.2 (A), S32.2
unnamed: D33.2 (A), S33.2
unnamed: D34.2 (A), S34.2
unnamed: D35.2 (A), S35.2
unnamed: D36.2 (A), S36.2
unnamed: R5.2, R8.1
unnamed: R9.1, SW2.2
unnamed: R4.1, U1.46 (USB_D_N)
unnamed: R3.1, U1.47 (USB_D_P)
ROW_0: D1.1 (K), D2.1 (K), D3.1 (K), D4.1 (K), D5.1 (K), D6.1 (K), D7.1 (K), D8.1 (K), D9.1 (K), D10.1 (K), U1.41 (GPIO29_ADC3)
ROW_1: D11.1 (K), D12.1 (K), D13.1 (K), D14.1 (K), D15.1 (K), D16.1 (K), D17.1 (K), D18.1 (K), D19.1 (K), D20.1 (K), U1.40 (GPIO28_ADC2)
ROW_2: D21.1 (K), D22.1 (K), D23.1 (K), D24.1 (K), D25.1 (K), D26.1 (K), D27.1 (K), D28.1 (K), D29.1 (K), D30.1 (K), U1.39 (GPIO27_ADC1)
ROW_3: D31.1 (K), D32.1 (K), D33.1 (K), D34.1 (K), D35.1 (K), D36.1 (K), U1.38 (GPIO26_ADC0)
RUN: R7.2, SW1.2, U1.26 (RUN)
SCLK: U1.52 (QSPI_SCLK), U2.6 (CLK)
SD1: U1.55 (QSPI_SD1), U2.2 (DO/IO_{1})
SD2: U1.54 (QSPI_SD2), U2.3 (~WP/IO_{2})
SD3: U1.51 (QSPI_SD3), U2.7 (~HOLD/~RESET/IO_{3})
SDO: U1.53 (QSPI_SD0), U2.5 (DI/IO_{0})
SEL: R8.2, R9.2, U1.56 (QSPI_SS), U2.1 (~CS)
SWCLK: TP21.1, U1.24 (SWCLK)
SWDIO: TP22.1, U1.25 (SWD)
X_IN: C14.2, U1.20 (XIN), Y1.1
X_OUT: R6.2, U1.21 (XOUT)
